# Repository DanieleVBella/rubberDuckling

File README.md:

# rubberDuckling
A very simple rubber ducky, designed to be entirely assemblable using the JLCPCB SMT service

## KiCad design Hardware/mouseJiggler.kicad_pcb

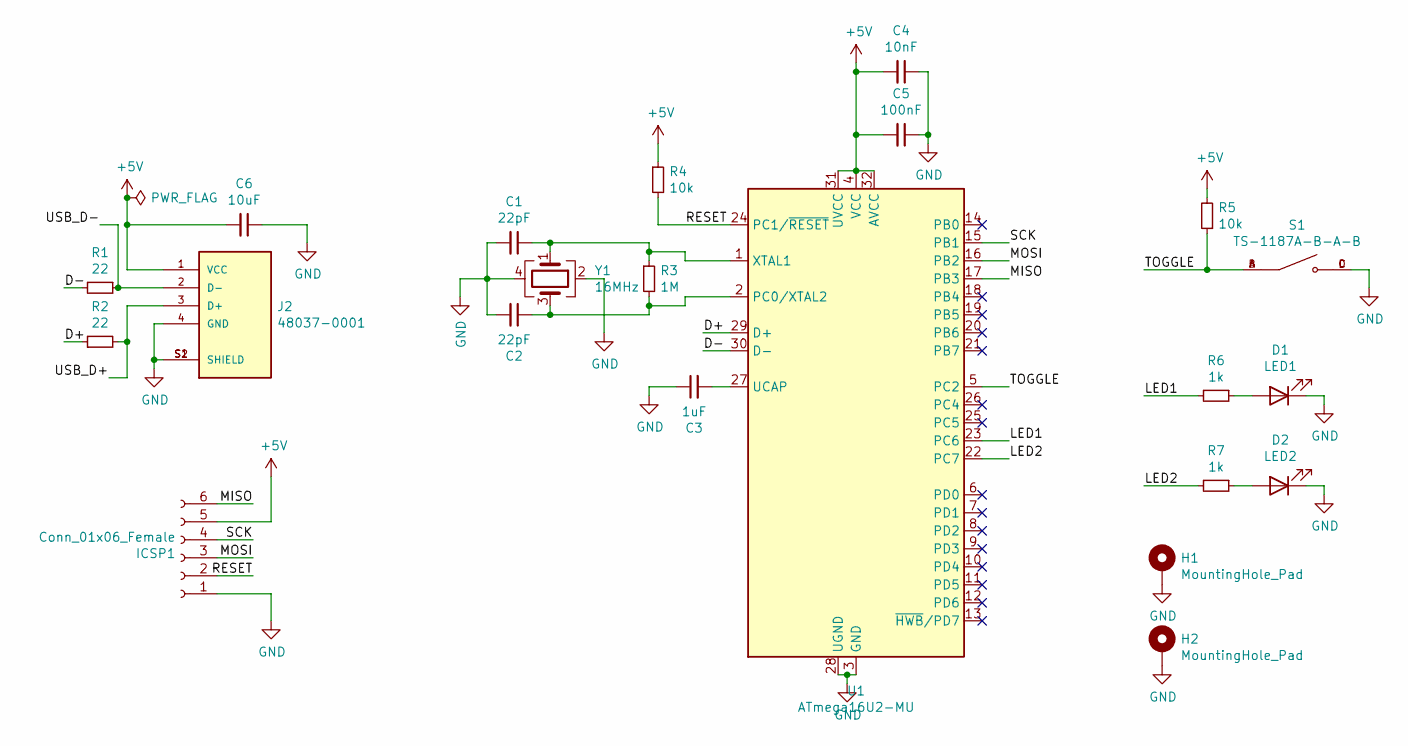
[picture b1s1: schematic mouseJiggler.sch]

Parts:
C1, C2: 22pF; C_0603_1608Metric
C3: 1uF; C_0603_1608Metric
C4: 10nF; C_0603_1608Metric
C5: 100nF; C_0603_1608Metric
C6: 10uF; C_0603_1608Metric
D1: LED1; D_0603_1608Metric
D2: LED2; D_0603_1608Metric
H1, H2: MountingHole_Pad; MountingHole_2.2mm_M2_DIN965_Pad
ICSP1: Conn_01x06_Female; PinHeader_2x03_P2.54mm_Vertical
J2: 48037-0001; MOLEX_48037-0001; PARTREV D
R1, R2: 22; R_0603_1608Metric
R3: 1M; R_0603_1608Metric
R4, R5: 10k; R_0603_1608Metric
R6, R7: 1k; R_0603_1608Metric
S1: TS-1187A-B-A-B; SW_TS-1187A-B-A-B; PARTREV A0
U1: ATmega16U2-MU; QFN-32-1EP_5x5mm_P0.5mm_EP3.1x3.1mm
Y1: 16MHz; Crystal_SMD_3225-4Pin_3.2x2.5mm

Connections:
+5V: C4.2, C5.2, C6.2, ICSP1.5, J2.1 (VCC), R4.1, R5.2, U1.4 (VCC), U1.31 (UVCC), U1.32 (AVCC)
/D+: R2.1, U1.29 (D+)
/D-: R1.2, U1.30 (D-)
/LED1: R6.2, U1.23 (PC6)
/LED2: R7.2, U1.22 (PC7)
/MISO: ICSP1.6, U1.17 (PB3)
/MOSI: ICSP1.3, U1.16 (PB2)
/RESET: ICSP1.2, R4.2, U1.24 (PC1/~RESET)
/SCK: ICSP1.4, U1.15 (PB1)
/TOGGLE: R5.1, S1.A, S1.B, U1.5 (PC2)
/USB_D+: J2.3 (D+), R2.2
/USB_D-: J2.2 (D-), R1.1
GND: C1.2, C2.2, C3.1, C4.1, C5.1, C6.1, D1.1 (K), D2.1 (K), H1.1, H2.1, ICSP1.1, J2.4 (GND), J2.S1 (SHIELD), J2.S2 (SHIELD), S1.C, S1.D, U1.3 (GND), U1.28 (UGND), U1.33 (GND), Y1.2, Y1.4
unnamed: C1.1, R3.1, U1.1 (XTAL1), Y1.1
unnamed: C2.1, R3.2, U1.2 (PC0/XTAL2), Y1.3
unnamed: C3.2, U1.27 (UCAP)
unnamed: D1.2 (A), R6.1
unnamed: D2.2 (A), R7.1

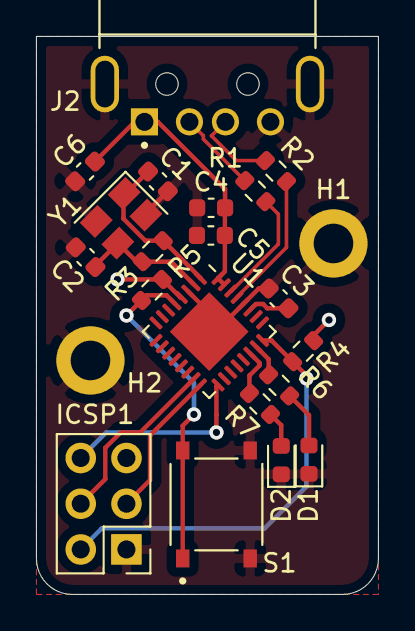
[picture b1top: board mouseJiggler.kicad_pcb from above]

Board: 2 copper layers, 19.0 x 31.0 mm, 22 parts (0 on the bottom side), 18 nets.

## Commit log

2021-11-29 Add project so far
2021-12-01 Updated and added silkscreen
2021-12-02 Updated USB and silkscreen
2021-12-03 Made final changes to silkscreen
2021-12-05 Updated PCB
2021-12-06 Added 3D file
2021-12-22 Moved PCB files to own Folder
2021-12-22 Added Firmware folder
2021-12-22 Add initial firmware
    Uses LUFA library. Code not working as of yet, but LEDS and Pins should be configured
2021-12-23 Code runs baby
2021-12-23 Fix LEDs and add toggle to button
2021-12-23 Make mouseJiggler work using hack
2021-12-23 Added fast click code
